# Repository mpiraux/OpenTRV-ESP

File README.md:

# OpenTRV-ESP

An open-source and open-hardware thermostatic radiator valve based on the ESP32C6 and the 28BYJ-48 stepper motor.

The design phase is [ongoing and documented](documentation/design_rationale.md).

## License

All the software source code is available under the [MIT license](https://choosealicense.com/licenses/mit/) while the hardware design files and derivatives are available under the [CERN Open Hardware Licence Version 2 - Permissive](LICENSE.md).

## Credits

Inspired by https://github.com/fabianmuehlberger/OpenValve.

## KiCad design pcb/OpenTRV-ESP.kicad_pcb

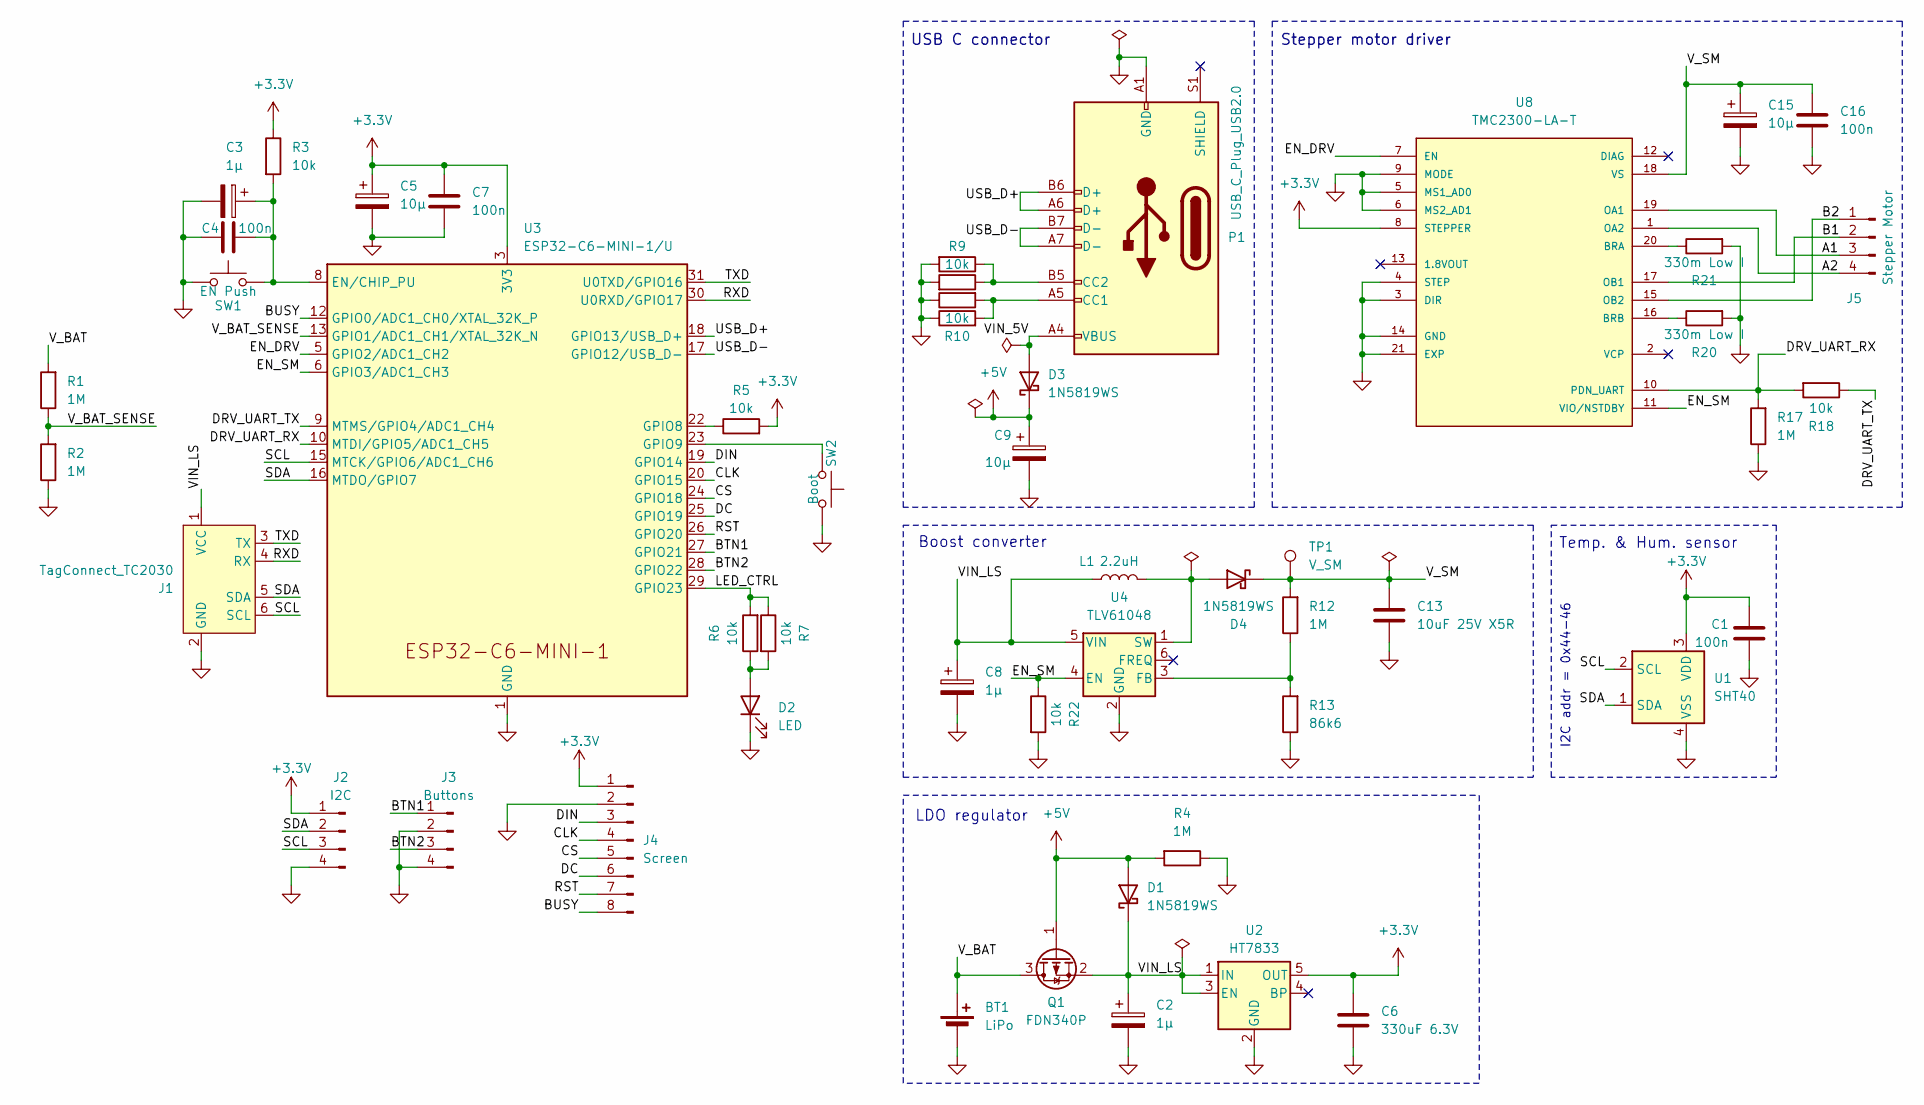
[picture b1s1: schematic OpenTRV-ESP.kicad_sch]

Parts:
BT1: LiPo; PinHeader_1x02_P2.54mm_Vertical
C1, C4, C7, C16: 100n; C_0402_1005Metric
C2, C3, C8: 1µ; C_0402_1005Metric
C5, C9, C15: 10µ; C_0603_1608Metric; LCSC Part # C596327
C6: 330uF 6.3V; CP_EIA-7343-20_Kemet-V; LCSC Part # C136150
C13: 10uF 25V X5R; C_0603_1608Metric; LCSC Part # C596327
D1, D3, D4: 1N5819WS; D_SOD-323
D2: LED; LED_0603_1608Metric
J1: TagConnect_TC2030; Tag-Connect_TC2030-IDC-FP_2x03_P1.27mm_Vertical
J2: I2C; PinHeader_1x04_P2.54mm_Vertical
J3: Buttons; PinHeader_1x04_P2.54mm_Vertical
J4: Screen; JST_PH_B8B-PH-K_1x08_P2.00mm_Vertical
J5: Stepper Motor; JST_XH_B4B-XH-A_1x04_P2.50mm_Vertical
L1: 2.2uH; L_Sunlord_SWPA5040S; LCSC Part # C96923
P1: USB_C_Plug_USB2.0; USB_C_Receptacle_XKB_U262-16XN-4BVC11
Q1: FDN340P; SOT-23
R1, R2, R4, R12, R17: 1M; R_0402_1005Metric
R3, R5, R6, R7, R8, R9, R10, R11, R18, R22: 10k; R_0402_1005Metric
R13: 86k6; R_0402_1005Metric
R20, R21: 330m Low I; R_1206_3216Metric
SW1: EN Push; DEALON_5.5x2m
SW2: Boot; DEALON_5.5x2m
TP1: V_SM; TestPoint_Pad_D1.5mm
U1: SHT40; Sensirion_DFN-4_1.5x1.5mm_P0.8mm_SHT4x_NoCentralPad
U2: HT7833; SOT-23-5
U3: ESP32-C6-MINI-1/U; ESP32-C6-MINI-1
U4: TLV61048; SOT-23-6; LCSC Part # C2861467
U8: TMC2300-LA-T; QFN40P300X300X90-21N

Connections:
+3.3V: C1.1, C5.1, C6.1, C7.1, J2.1, J4.1, R3.1, R5.2, U1.3 (VDD), U2.5 (OUT), U3.3 (3V3), U8.8 (STEPPER)
+5V: C9.1, D1.2 (A), D3.1 (K), Q1.1 (G), R4.2
/A1: J5.3, U8.19 (OA1)
/A2: J5.4, U8.1 (OA2)
/B1: J5.2, U8.17 (OB1)
/B2: J5.1, U8.15 (OB2)
/BTN1: J3.1, U3.27 (GPIO21)
/BTN2: J3.3, U3.28 (GPIO22)
/BUSY: J4.8, U3.12 (GPIO0/ADC1_CH0/XTAL_32K_P)
/CLK: J4.4, U3.20 (GPIO15)
/CS: J4.5, U3.24 (GPIO18)
/DC: J4.6, U3.25 (GPIO19)
/DIN: J4.3, U3.19 (GPIO14)
/DRV_UART_RX: R17.2, R18.2, U3.10 (MTDI/GPIO5/ADC1_CH5), U8.10 (PDN_UART)
/DRV_UART_TX: R18.1, U3.9 (MTMS/GPIO4/ADC1_CH4)
/EN_DRV: U3.5 (GPIO2/ADC1_CH2), U8.7 (EN)
/EN_SM: R22.1, U3.6 (GPIO3/ADC1_CH3), U4.4 (EN), U8.11 (VIO/NSTDBY)
/LED_CTRL: R6.2, R7.1, U3.29 (GPIO23)
/RST: J4.7, U3.26 (GPIO20)
/RXD: J1.4 (RX), U3.30 (U0RXD/GPIO17)
/SCL: J1.6 (SCL), J2.3, U1.2 (SCL), U3.15 (MTCK/GPIO6/ADC1_CH6)
/SDA: J1.5 (SDA), J2.2, U1.1 (SDA), U3.16 (MTDO/GPIO7)
/TXD: J1.3 (TX), U3.31 (U0TXD/GPIO16)
/USB_D+: P1.A6 (D+), P1.B6 (D+), U3.18 (GPIO13/USB_D+)
/USB_D-: P1.A7 (D-), P1.B7 (D-), U3.17 (GPIO12/USB_D-)
/VIN_5V: D3.2 (A), P1.A4 (VBUS), P1.A9 (VBUS), P1.B4 (VBUS), P1.B9 (VBUS)
/VIN_LS: C2.1, C8.1, D1.1 (K), J1.1 (VCC), L1.1, Q1.2 (S), U2.1 (IN), U2.3 (EN), U4.5 (VIN)
/V_BAT: BT1.1 (+), Q1.3 (D), R1.2
/V_BAT_SENSE: R1.1, R2.2, U3.13 (GPIO1/ADC1_CH1/XTAL_32K_N)
/V_SM: C13.1, C15.1, C16.1, D4.1 (K), R12.2, TP1.1, U8.18 (VS)
GND: BT1.2 (-), C1.2, C2.2, C3.2, C4.1, C5.2, C6.2, C7.2, C8.2, C9.2, C13.2, C15.2, C16.2, D2.1 (K), J1.2 (GND), J2.4, J3.2, J3.4, J4.2, P1.A1 (GND), P1.A12 (GND), P1.B1 (GND), P1.B12 (GND), R2.1, R4.1, R8.2, R9.2, R10.1, R11.1, R13.1, R17.1, R20.2, R21.2, R22.2, SW1.1, SW2.2, U1.4 (VSS), U2.2 (GND), U3.1 (GND), U3.2 (GND), U3.11 (GND), U3.14 (GND), U3.36 (GND), U3.37 (GND), U3.38 (GND), U3.39 (GND), U3.40 (GND), U3.41 (GND), U3.42 (GND), U3.43 (GND), U3.44 (GND), U3.45 (GND), U3.46 (GND), U3.47 (GND), U3.48 (GND), U3.49 (GND), U3.50 (GND), U3.51 (GND), U3.52 (GND), U3.53 (GND), U4.2 (GND), U8.3 (DIR), U8.4 (STEP), U8.5 (MS1_AD0), U8.6 (MS2_AD1), U8.9 (MODE), U8.14 (GND), U8.21 (EXP)
unnamed: D2.2 (A), R6.1, R7.2
unnamed: D4.2 (A), L1.2, U4.1 (SW)
unnamed: P1.A5 (CC1), R10.2, R11.2
unnamed: P1.B5 (CC2), R8.1, R9.1
unnamed: C3.1, C4.2, R3.2, SW1.2, U3.8 (EN/CHIP_PU)
unnamed: R5.1, U3.22 (GPIO8)
unnamed: SW2.1, U3.23 (GPIO9)
unnamed: R12.1, R13.2, U4.3 (FB)
unnamed: R21.1, U8.20 (BRA)
unnamed: R20.1, U8.16 (BRB)

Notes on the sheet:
Boost converter
Temp. & Hum. sensor
USB C connector
LDO regulator
I2C addr = 0x44-46
Stepper motor driver

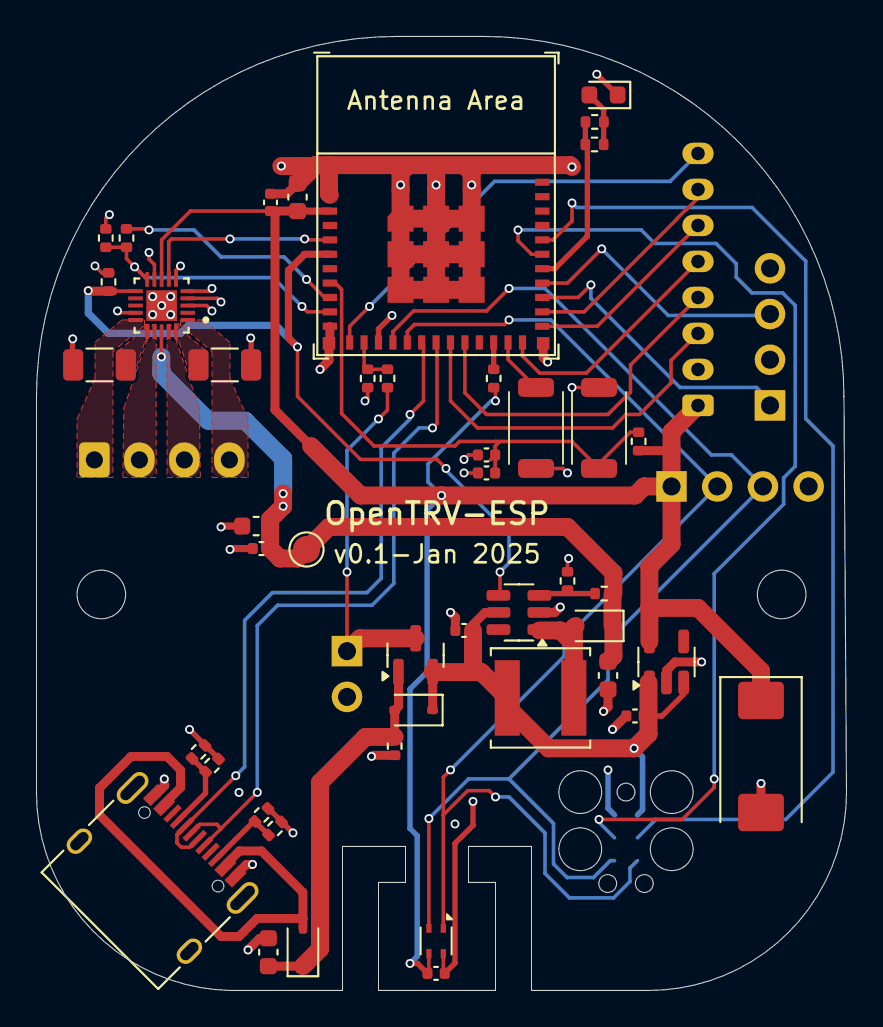
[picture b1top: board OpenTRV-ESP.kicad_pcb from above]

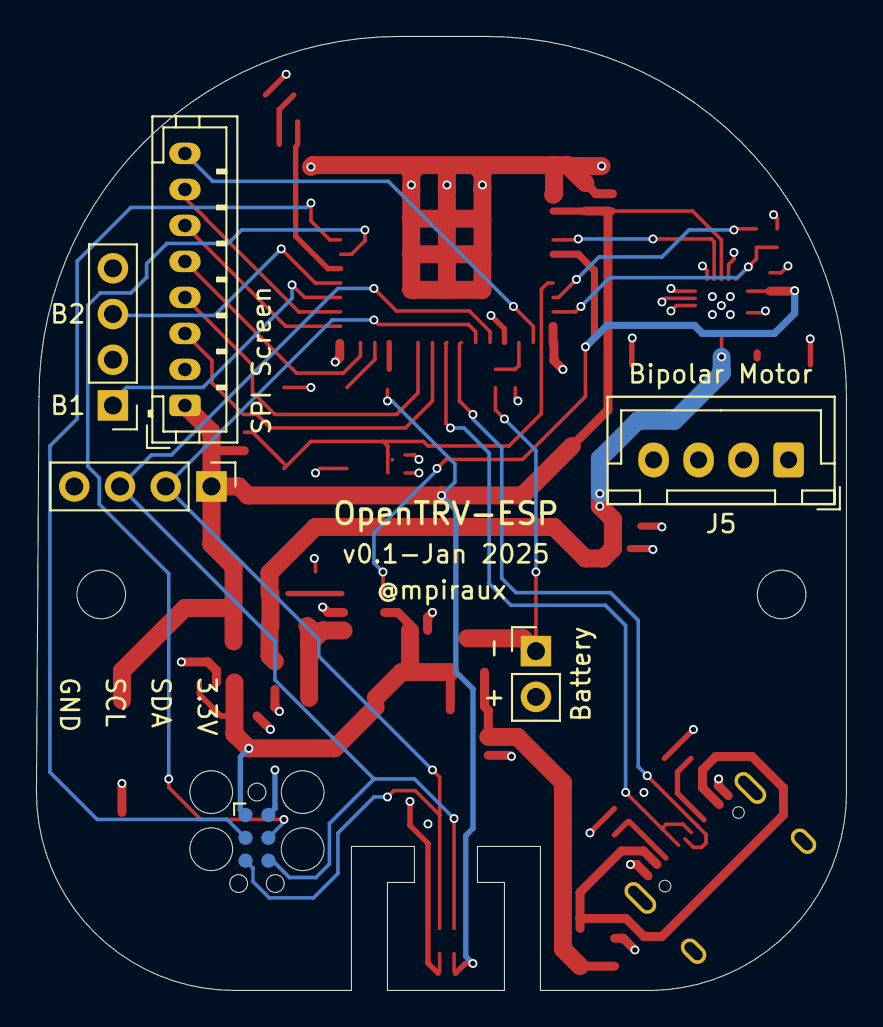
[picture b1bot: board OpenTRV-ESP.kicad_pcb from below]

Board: 4 copper layers, 45.0 x 53.0 mm, 51 parts (6 on the bottom side), 41 nets.

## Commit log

2025-01-20 Adds a holder to the back of the motor to strengthen the assembly
2025-01-21 Reconnects the stepper driver to the ESP ULP pins
    Redoes the board layout and routing.
    The temperature sensor is now centered at the bottom of the board.
2025-01-22 Improves the M30 mounting nut
2025-02-15 WIP TMC2300
